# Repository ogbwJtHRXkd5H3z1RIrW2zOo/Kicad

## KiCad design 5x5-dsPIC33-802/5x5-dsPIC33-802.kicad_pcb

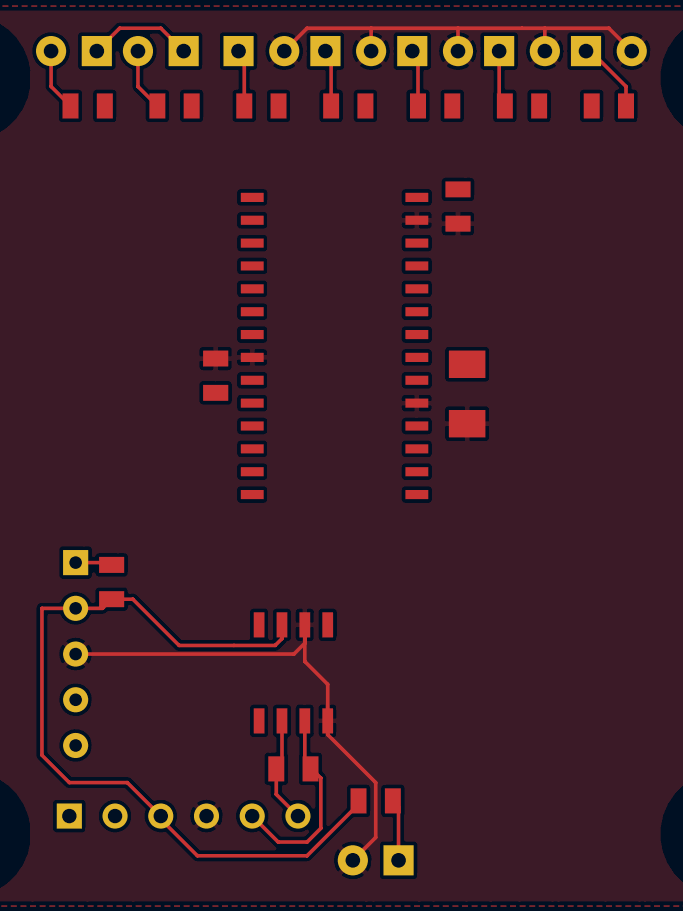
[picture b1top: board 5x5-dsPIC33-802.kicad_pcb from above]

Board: 2 copper layers, 29 parts (0 on the bottom side), 23 nets.

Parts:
3.3V1: LED; Ogbw-LED-3MM
BtB1: CONN_6; Ogbw-PIN_ARRAY-6X1-droit
CAN1: SN65HVD230D; Ogbw-SOIC-8
CAN_RX1: LED; Ogbw-LED-3MM
CAN_TX1: LED; Ogbw-LED-3MM
Cp1: C; Ogbw-CMS-1206
Cp2, Cp3: C; Ogbw-CMS-0805
D0, D1, D2, D3, D4: LED; Ogbw-LED-3MM
DSPIC33: DSPIC33FJXXXMC802; Ogbw-SOIC-28
ICSP1: CONN_5; Ogbw-PIN_ARRAY-5X1-coudée
R3, R4, R6: R; Ogbw-CMS-0805
Rc1: R; Ogbw-CMS-0805
Rd0, Rd1, Rd2, Rd3, Rd4: R; Ogbw-CMS-0805
Rp1: R; Ogbw-CMS-0805
T1, T2, T3, T4: TROU; Ogbw-Trou-mécanique

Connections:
+3.3V: BtB1.3, CAN1.3, CAN_RX1.1, CAN_TX1.1, Cp2.2, Cp3.2, DSPIC33.13, DSPIC33.28, ICSP1.2, R6.1, Rp1.2
/CANH: BtB1.5, CAN1.7, Rc1.1
/CANL: BtB1.6, CAN1.6, Rc1.2
/CAN_RX: CAN1.4, DSPIC33.16, R4.1
/CAN_TX: CAN1.1, DSPIC33.15, R3.1
/D0: DSPIC33.2, Rd0.1
/D1: DSPIC33.3, Rd1.1
/D2: DSPIC33.9, Rd2.1
/D3: DSPIC33.10, Rd3.1
/D4: DSPIC33.12, Rd4.1
/MCLR: DSPIC33.1, ICSP1.1, Rp1.1
/PGC: DSPIC33.5, ICSP1.5
/PGD: DSPIC33.4, ICSP1.4
unnamed: D4.1, Rd4.2
unnamed: D3.1, Rd3.2
unnamed: CAN_TX1.2, R3.2
unnamed: CAN_RX1.2, R4.2
unnamed: D0.1, Rd0.2
unnamed: D1.1, Rd1.2
unnamed: D2.1, Rd2.2
unnamed: 3.3V1.1, R6.2
unnamed: Cp1.1, DSPIC33.20
VSS: 3.3V1.2, BtB1.4, CAN1.2, CAN1.8, Cp1.2, Cp2.1, Cp3.1, D0.2, D1.2, D2.2, D3.2, D4.2, DSPIC33.8, DSPIC33.19, DSPIC33.27, ICSP1.3

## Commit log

2015-03-29 :confetti_ball: Added .gitattributes & .gitignore files
2015-03-29 Components and footprints libraries
    Contains component descriptions for eeschema and footprints for pcbnew.
    These files will be updated each time I use a new component on my
    designs.
2015-03-29 5x5 cm model board
    Model for a standart 5x5cm board with a dsPIC on it.
    Contains mandatory modules and connections in eeschema, and board
    contour in pcbnew.
